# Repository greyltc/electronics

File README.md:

# solar-sim-electronics
KiCAD electrical circuit design and PCB layout files for solar cell measurement equipment

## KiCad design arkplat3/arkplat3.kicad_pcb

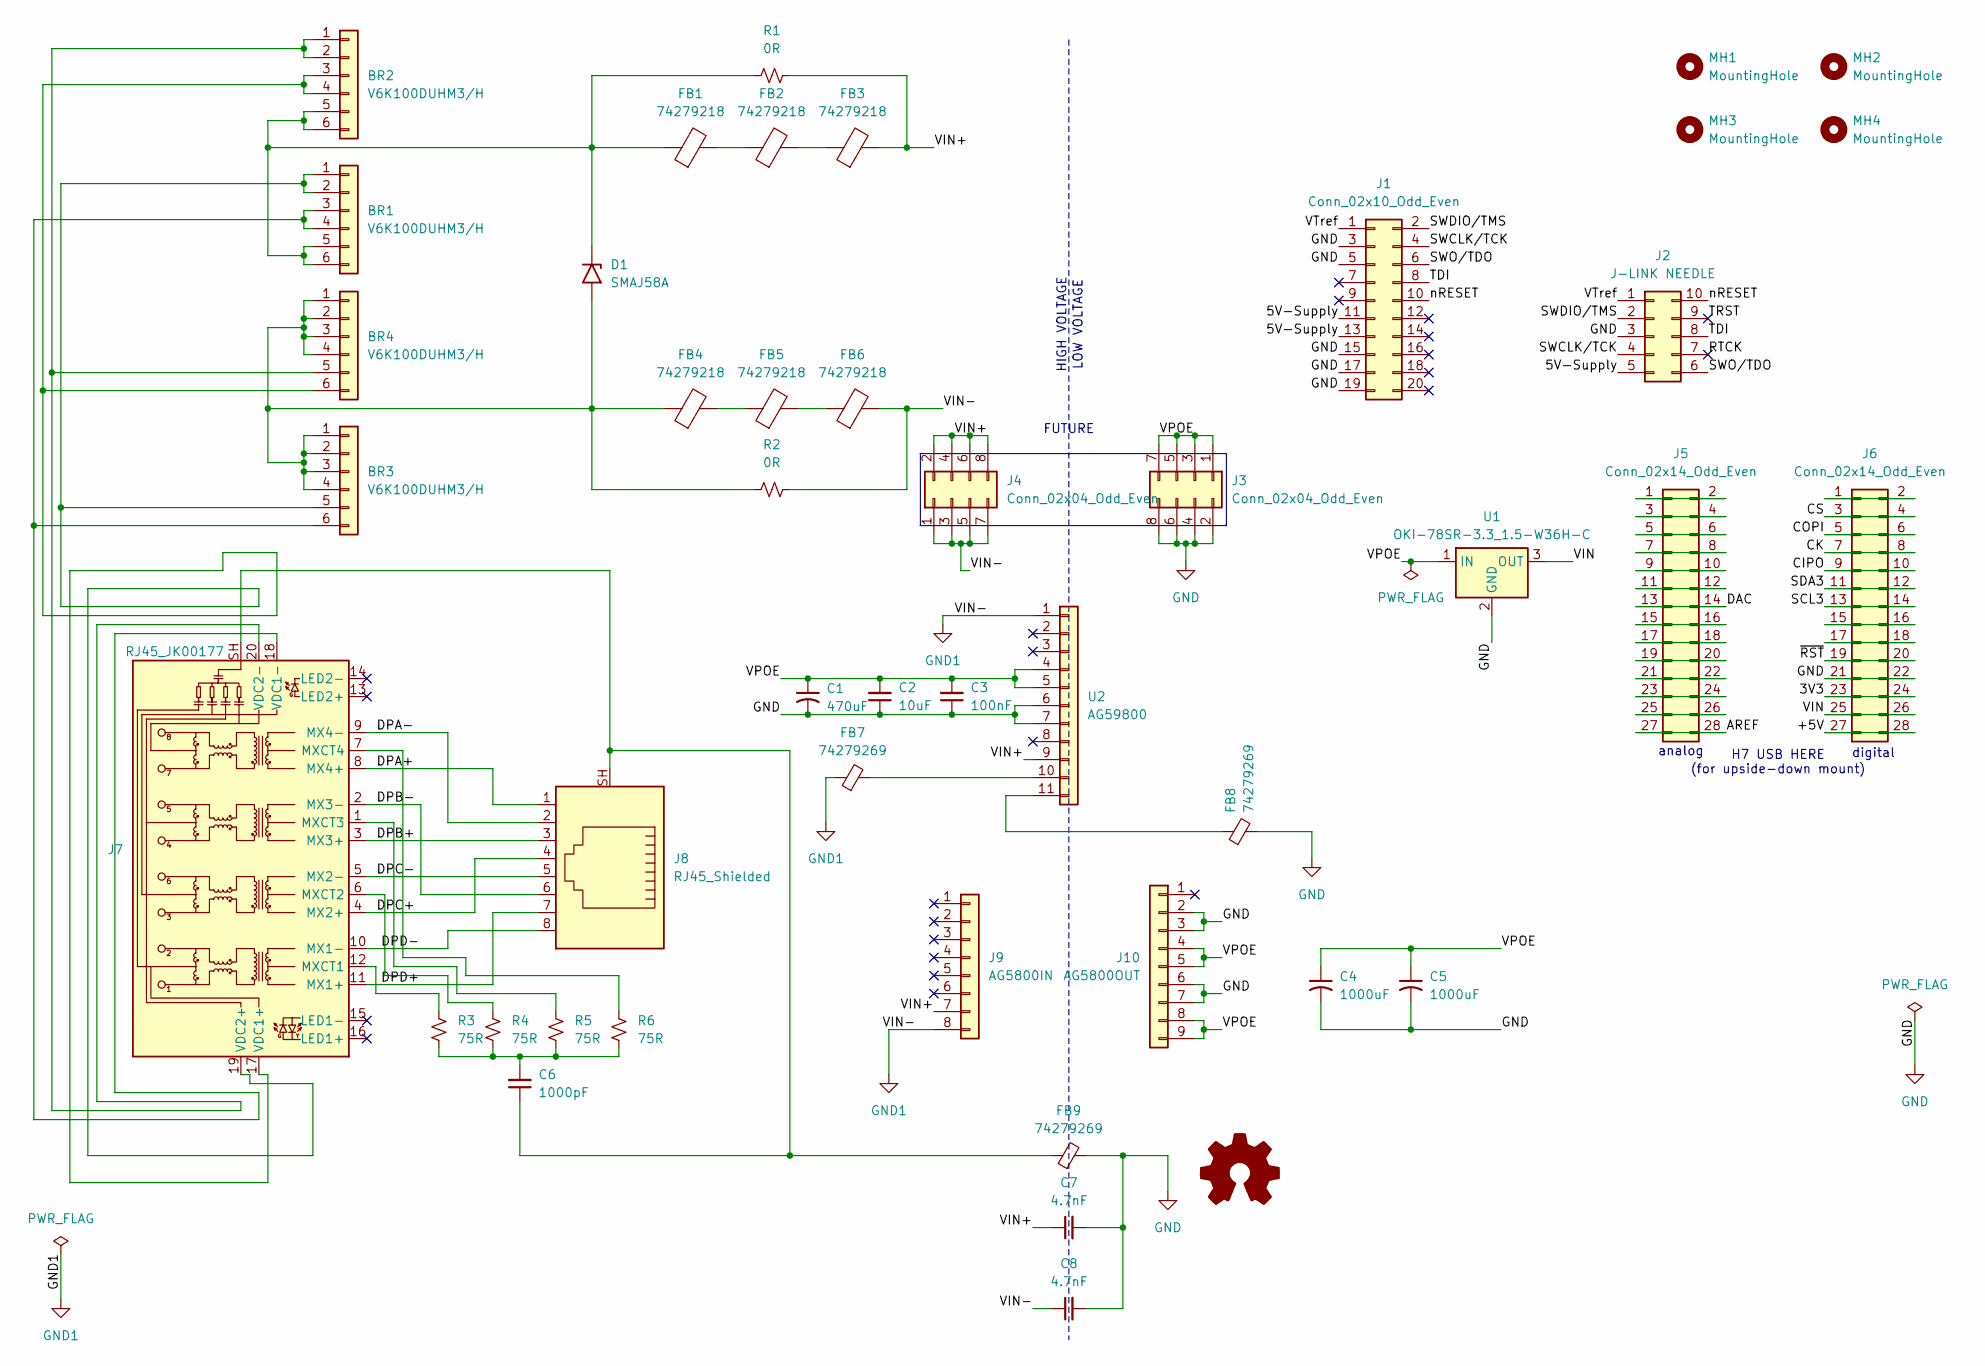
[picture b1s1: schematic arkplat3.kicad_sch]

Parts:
BR1, BR2, BR3, BR4: V6K100DUHM3/H; PowerPAK_SO-8_Dual
C1: 470uF; CP_Radial_D10.0mm_P5.00mm
C2: 10uF; C_1206_3216Metric_Pad1.33x1.80mm_HandSolder
C3: 100nF; C_1206_3216Metric_Pad1.33x1.80mm_HandSolder
C4, C5: 1000uF; CP_Radial_D10.0mm_P5.00mm
C6: 1000pF; C_1206_3216Metric_Pad1.33x1.80mm_HandSolder
C7, C8: 4.7nF; C_1206_3216Metric_Pad1.33x1.80mm_HandSolder
D1: SMAJ58A; D_SMA
FB1, FB2, FB3, FB4, FB5, FB6: 74279218; L_1206_3216Metric_Pad1.22x1.90mm_HandSolder
FB7, FB8, FB9: 74279269; L_0603_1608Metric_Pad1.05x0.95mm_HandSolder
J1: Conn_02x10_Odd_Even; PinHeader_2x10_P1.27mm_Vertical_SMD
J2: J-LINK NEEDLE; Tag-Connect_TC2050-IDC-FP_2x05_P1.27mm_Vertical
J3, J4: Conn_02x04_Odd_Even; PinSocket_2x04_P2.54mm_Vertical
J5, J6: Conn_02x14_Odd_Even; PinSocket_2x14_P2.54mm_Vertical
J7: RJ45_JK00177; RJ45_Pulse_JK00177NL_Horizontal
J8: RJ45_Shielded; RJ45_Molex_0855135013_Vertical
J9: AG5800IN; PinSocket_1x08_P2.54mm_Vertical
J10: AG5800OUT; PinSocket_1x09_P2.54mm_Vertical
MH1, MH2, MH3, MH4: MountingHole; MountingHole_2.7mm_M2.5_ISO14580
R1, R2: 0R; R_1206_3216Metric_Pad1.30x1.75mm_HandSolder
R3, R4, R5, R6: 75R; R_1206_3216Metric_Pad1.30x1.75mm_HandSolder
SYM1: Logo_Open_Hardware_Small; site_small
U1: OKI-78SR-3.3_1.5-W36H-C; Converter_DCDC_Murata_OKI-78SR_Horizontal
U2: AG59800; AG59800-LPB

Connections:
/3V3: J6.23, J6.24
/5V-Supply: J1.11, J1.13, J2.5
/+5V: J6.27, J6.28
/AREF: J5.27, J5.28
/CIPO: J6.9, J6.10
/CK: J6.7, J6.8
/COPI: J6.5, J6.6
/CS: J6.3, J6.4
/DAC: J5.13, J5.14
/DPA+: J7.8 (MX4+), J8.1
/DPA-: J7.9 (MX4-), J8.2
/DPB+: J7.3 (MX3+), J8.3
/DPB-: J7.2 (MX3-), J8.6
/DPC+: J7.4 (MX2+), J8.4
/DPC-: J7.5 (MX2-), J8.5
/DPD+: J7.11 (MX1+), J8.7
/DPD-: J7.10 (MX1-), J8.8
/RTCK: J2.7
/SCL3: J6.13, J6.14
/SDA3: J6.11, J6.12
/SWCLK/TCK: J1.4, J2.4
/SWDIO/TMS: J1.2, J2.2
/SWO/TDO: J1.6, J2.6
/TDI: J1.8, J2.8
/TRST: J2.9
/VIN: J6.25, J6.26, U1.3 (OUT)
/VIN+: C7.1, FB3.2, J4.2, J4.4, J4.6, J4.8, J9.7, R1.2, U2.9
/VPOE: C1.1, C2.2, C3.2, C4.1, C5.1, J3.1, J3.3, J3.5, J3.7, J10.4, J10.5, J10.8, J10.9, U1.1 (IN), U2.4, U2.5
/VTref: J1.1, J2.1
/nRESET: J1.10, J2.10
/~RST: J6.19, J6.20
GND: C1.2, C2.1, C3.1, C4.2, C5.2, C7.2, C8.2, FB8.2, FB9.2, J1.3, J1.5, J1.15, J1.17, J1.19, J2.3, J3.2, J3.4, J3.6, J3.8, J6.21, J6.22, J10.2, J10.3, J10.6, J10.7, U1.2 (GND), U2.6, U2.7
GND1: C8.1, FB6.2, FB7.1, J4.1, J4.3, J4.5, J4.7, J9.8, R2.2, U2.1
unnamed: BR1.1, BR1.2, BR3.5, J7.19 (VDC2+)
unnamed: BR1.3, BR1.4, BR3.6, J7.18 (VDC1-)
unnamed: BR1.5, BR1.6, BR2.5, BR2.6, D1.1 (A1), FB1.1, R1.1
unnamed: BR2.1, BR2.2, BR4.5, J7.20 (VDC2-)
unnamed: BR2.3, BR2.4, BR4.6, J7.17 (VDC1+)
unnamed: BR3.1, BR3.2, BR3.3, BR3.4, BR4.1, BR4.2, BR4.3, BR4.4, D1.2 (A2), FB4.1, R2.1
unnamed: C6.1, FB9.1, J7.SH, J8.SH
unnamed: C6.2, R3.2, R4.2, R5.2, R6.2
unnamed: FB1.2, FB2.1
unnamed: FB2.2, FB3.1
unnamed: FB4.2, FB5.1
unnamed: FB5.2, FB6.1
unnamed: J5.1, J5.2
unnamed: J5.3, J5.4
unnamed: J5.5, J5.6
unnamed: J5.7, J5.8
unnamed: J5.9, J5.10
unnamed: J5.11, J5.12
unnamed: J5.15, J5.16
unnamed: J5.17, J5.18
unnamed: J5.19, J5.20
unnamed: J5.21, J5.22
unnamed: J5.23, J5.24
unnamed: J5.25, J5.26
unnamed: J6.1, J6.2
unnamed: J6.15, J6.16
unnamed: J6.17, J6.18
unnamed: J7.12 (MXCT1), R3.1
unnamed: J7.6 (MXCT2), R4.1
unnamed: J7.1 (MXCT3), R5.1
unnamed: J7.7 (MXCT4), R6.1
unnamed: FB7.2, U2.10
unnamed: FB8.1, U2.11

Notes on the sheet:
FUTURE
LOW VOLTAGE
H7 USB HERE (for upside-down mount)
digital
HIGH VOLTAGE
analog

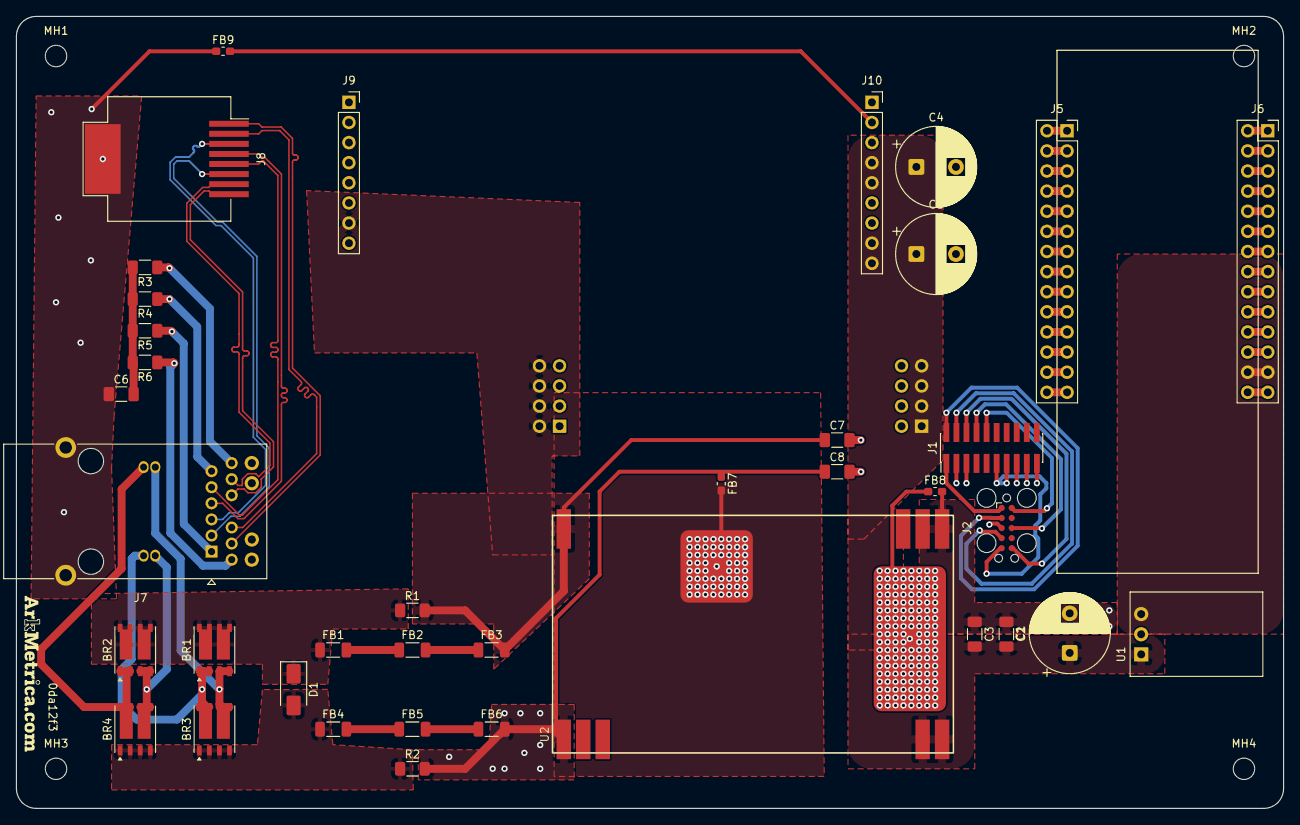
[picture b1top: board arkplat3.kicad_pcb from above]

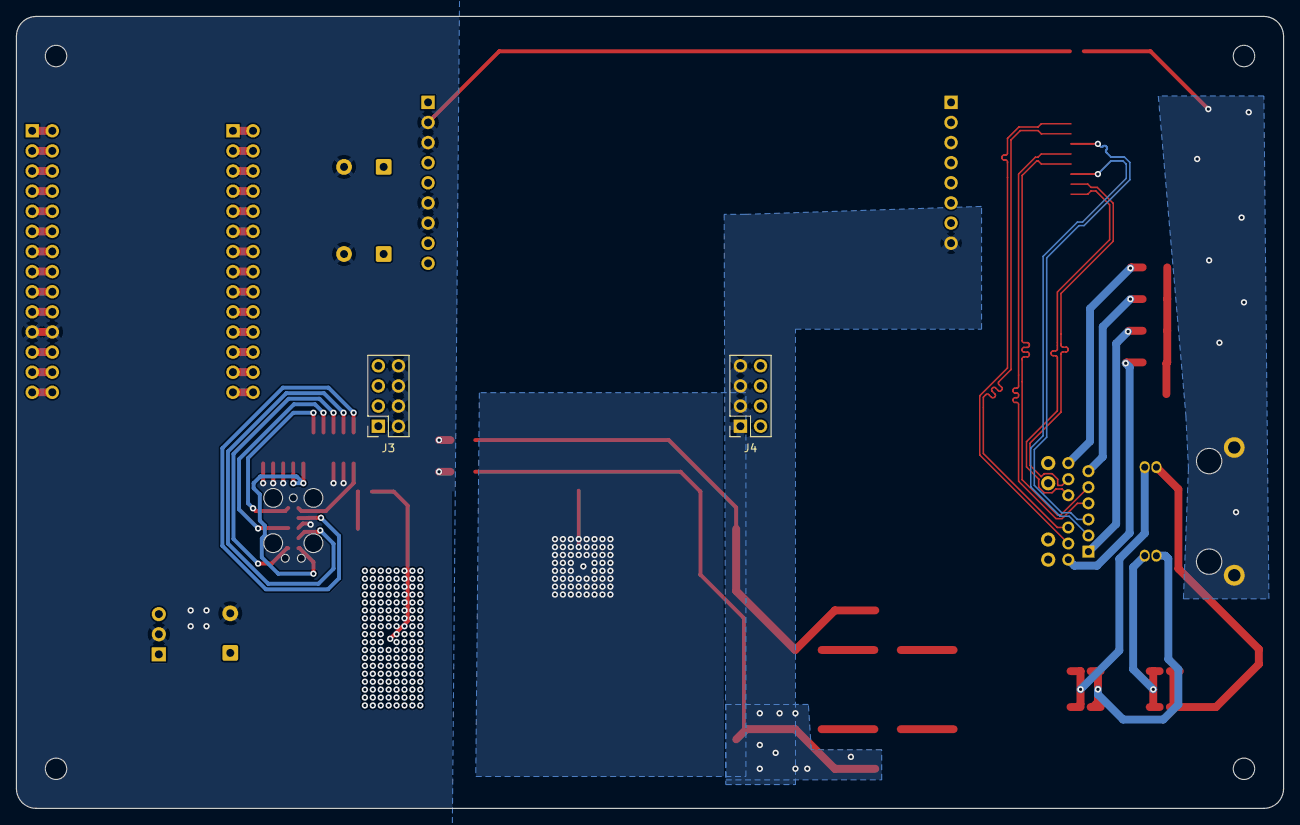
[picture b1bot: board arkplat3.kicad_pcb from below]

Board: 2 copper layers, 160.0 x 100.0 mm, 45 parts (2 on the bottom side), 64 nets.

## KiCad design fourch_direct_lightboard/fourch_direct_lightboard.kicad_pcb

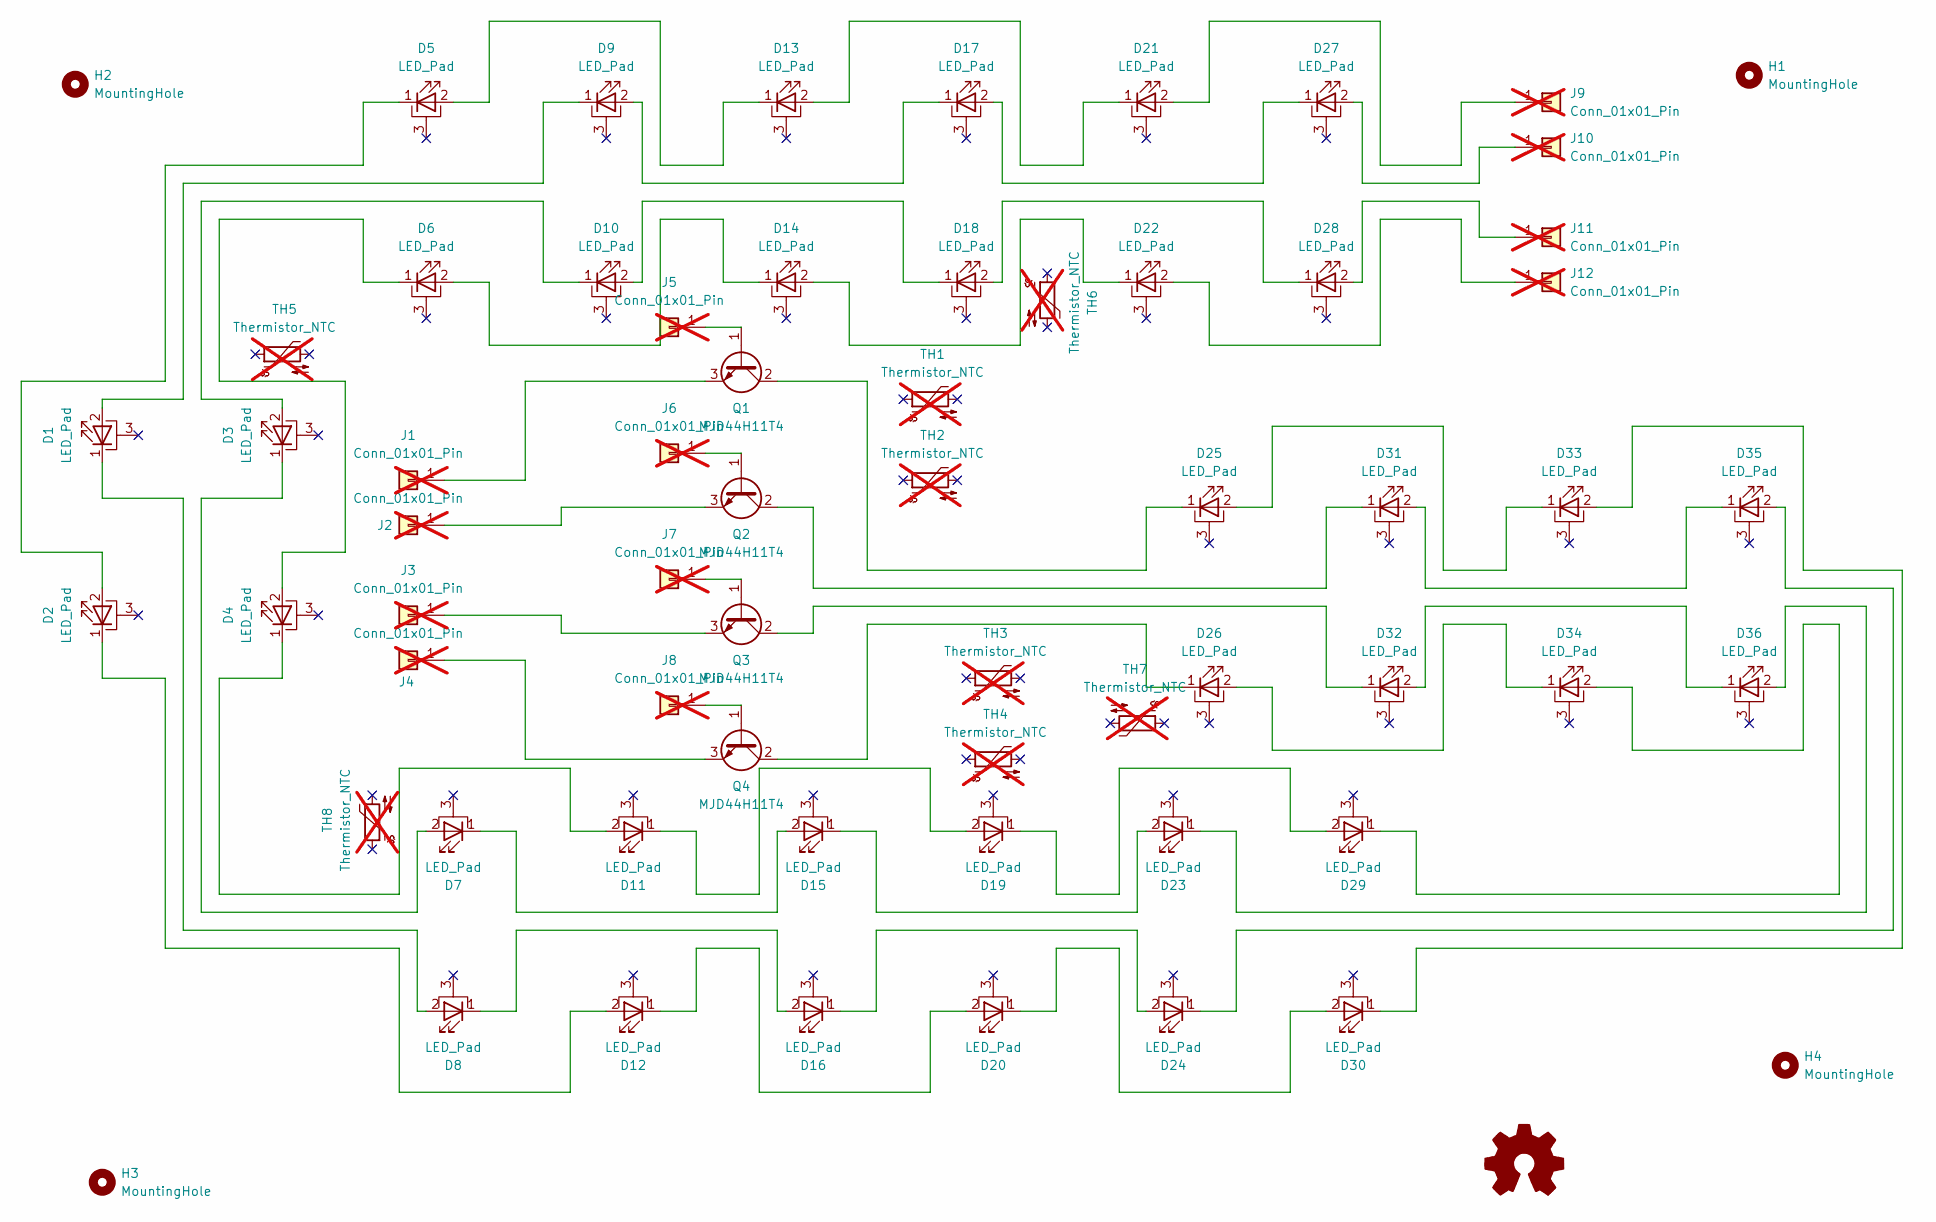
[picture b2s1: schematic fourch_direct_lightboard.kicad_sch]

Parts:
D1, D2, D3, D4, D5, D6, D7, D8, D9, D10, D11, D12, D13, D14, D15, D16, D17, D18, D19, D20, D21, D22, D23, D24, D25, D26, D27, D28, D29, D30, D31, D32, D33, D34, D35, D36: LED_Pad; LED_3x3_DIRECT_CU
H1, H2, H3, H4: MountingHole; MountingHole_3.50mm
J1, J2, J3, J4, J5, J6, J7, J8, J9, J10, J11, J12: Conn_01x01_Pin; TestPoint_Pad_D1.5mm; not fitted
Q1, Q2, Q3, Q4: MJD44H11T4; TO-252-2
SYM4: Logo_Open_Hardware_Small; site_small
TH1, TH2, TH3, TH4, TH5, TH6, TH7, TH8: Thermistor_NTC; R_0805_2012Metric_Pad1.20x1.40mm_HandSolder; not fitted

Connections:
unnamed: D1.2 (A), D9.1 (K)
unnamed: D1.1 (K), D8.2 (A)
unnamed: D2.2 (A), D5.1 (K)
unnamed: D3.1 (K), D7.2 (A)
unnamed: D4.2 (A), D6.1 (K)
unnamed: D10.2 (A), D18.1 (K)
unnamed: D3.2 (A), D10.1 (K)
unnamed: D4.1 (K), D11.2 (A)
unnamed: D11.1 (K), D19.2 (A)
unnamed: D2.1 (K), D12.2 (A)
unnamed: D12.1 (K), D20.2 (A)
unnamed: D13.2 (A), D21.1 (K)
unnamed: D5.2 (A), D13.1 (K)
unnamed: D14.2 (A), D22.1 (K)
unnamed: D6.2 (A), D14.1 (K)
unnamed: D7.1 (K), D15.2 (A)
unnamed: D15.1 (K), D23.2 (A)
unnamed: D8.1 (K), D16.2 (A)
unnamed: D16.1 (K), D24.2 (A)
unnamed: D17.2 (A), D27.1 (K)
unnamed: D9.2 (A), D17.1 (K)
unnamed: D18.2 (A), D28.1 (K)
unnamed: D19.1 (K), D29.2 (A)
unnamed: D20.1 (K), D30.2 (A)
unnamed: D21.2 (A), J9.1
unnamed: D22.2 (A), J12.1
unnamed: D23.1 (K), D36.2 (A)
unnamed: D24.1 (K), D35.2 (A)
unnamed: D25.2 (A), D33.1 (K)
unnamed: D25.1 (K), Q1.2 (C)
unnamed: D26.2 (A), D34.1 (K)
unnamed: D26.1 (K), Q4.2 (C)
unnamed: D27.2 (A), J10.1
unnamed: D28.2 (A), J11.1
unnamed: D29.1 (K), D34.2 (A)
unnamed: D30.1 (K), D33.2 (A)
unnamed: D31.2 (A), D35.1 (K)
unnamed: D31.1 (K), Q2.2 (C)
unnamed: D32.2 (A), D36.1 (K)
unnamed: D32.1 (K), Q3.2 (C)
unnamed: J1.1, Q1.3 (E)
unnamed: J2.1, Q2.3 (E)
unnamed: J3.1, Q3.3 (E)
unnamed: J4.1, Q4.3 (E)
unnamed: J5.1, Q1.1 (B)
unnamed: J6.1, Q2.1 (B)
unnamed: J7.1, Q3.1 (B)
unnamed: J8.1, Q4.1 (B)

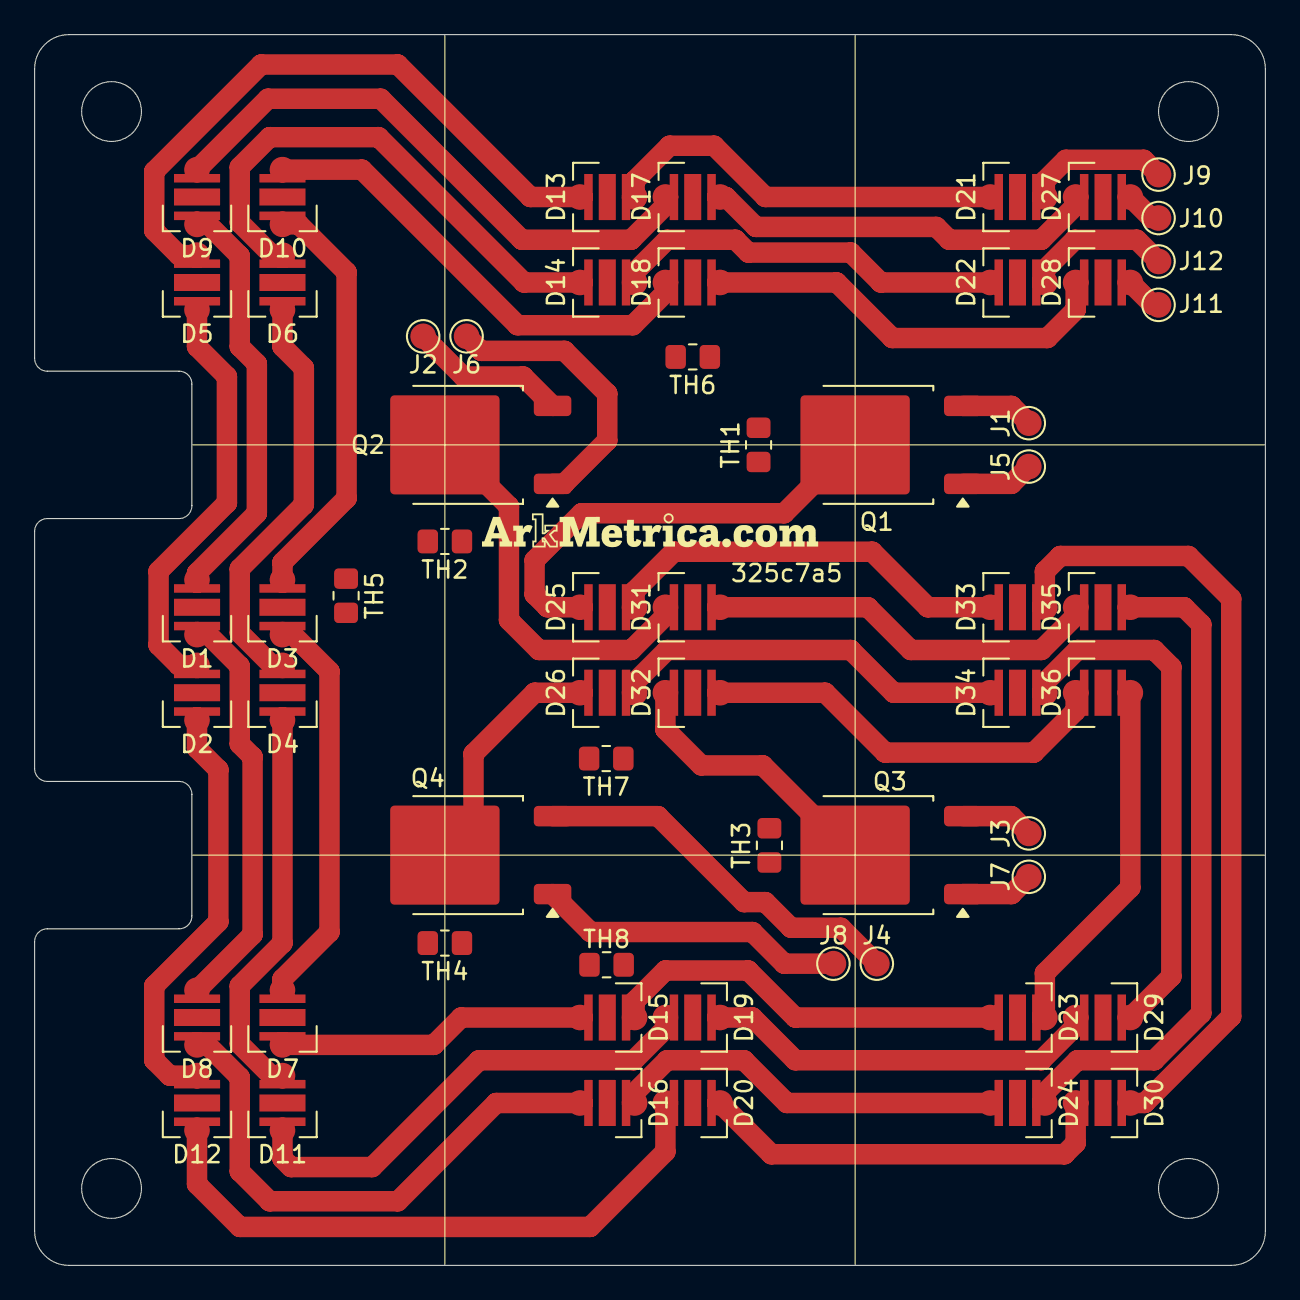
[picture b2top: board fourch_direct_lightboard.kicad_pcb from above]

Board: 2 copper layers, 72.0 x 72.0 mm, 65 parts (0 on the bottom side), 48 nets.

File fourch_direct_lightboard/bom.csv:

Comment,Designator,Footprint,LCSC Part Number
SST-10-UV-B130-F365-00,"D21,D13,D5,D2,D12,D20,D30,D33,D25",1212 LED THERMAL PAD,C6496960
SST-10-IRD-B130H-S810,"D27,D17,D9,D1,D8,D16,D24,D35,D31",1212 LED THERMAL PAD,C5291399
SST-10-IRD-B130H-S940,"D28,D18,D10,D3,D7,D15,D23,D36,D32",1212 LED THERMAL PAD,C7322031
GW CSSRM3.CM-M9N4-XX53-1-700-R18,"D22,D14,D6,D4,D11,D19,D29,D34,D26",1212 LED THERMAL PAD,C17379658
NSS1C301ET4G,"Q1,Q2,Q3,Q4",TO-252(DPAK),C463629

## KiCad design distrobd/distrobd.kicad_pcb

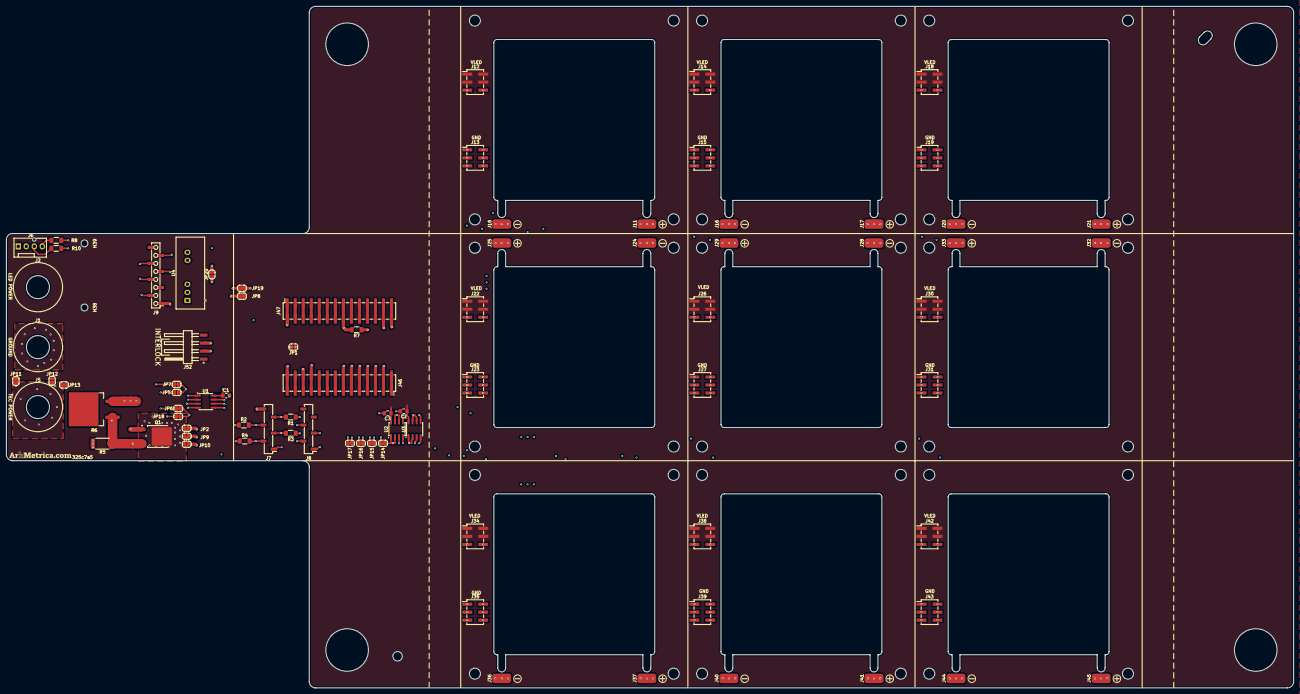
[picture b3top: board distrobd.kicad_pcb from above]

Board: 4 copper layers, 408.0 x 216.0 mm, 125 parts (0 on the bottom side), 58 nets.

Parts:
C1, C2, C3: 0.1uF; C_0805_2012Metric_Pad1.18x1.45mm_HandSolder
H1, H2, H3, H4, H5, H6, H7, H8, H9, H10, H11, H12, H13, H14, H15, H16, H17, H18, H19, H20, H21, H22, H23, H24, H25, H26, H27, H28, H29, H30, H31, H32, H33, H34, H35, H36: MountingHole; MountingHole_3.50mm
H37: MountingHole; MountingHole_3.0mm
H38, H39: MountingHole; MountingHole_2.2mm_M2
H40, H41, H42, H43: MountingHole; 13.5mm_NPTH
J1, J2, J5: Conn_01x01; LF994006
J6: Conn_01x04; FanPinHeader_1x04_P2.54mm_Vertical
J7, J8: Conn_01x06; PinSocket_1x06_P2.54mm_Vertical_SMD_Pin1Left
J9: Conn_01x08; PinSocket_1x08_P2.54mm_Vertical_SMD_Pin1Left
J10, J11, J16, J17, J20, J21, J24, J25, J28, J29, J32, J33, J36, J37, J40, J41, J44, J45: Conn_01x01; SolderWirePad_1x01_SMD_3x6mm
J12, J13, J14, J15, J18, J19, J22, J23, J26, J27, J30, J31, J34, J35, J38, J39, J42, J43: Conn_02x03_Odd_Even; PinHeader_2x03_P2.54mm_Vertical_SMD
J46, J47: Conn_02x14_Top_Bottom; PinSocket_2x14_P2.54mm_Vertical_SMD
J52: Conn_01x04; Harwin_M20-89004xx_1x04_P2.54mm_Horizontal
JP1, JP6, JP7: SolderJumper_2_Bridged; SolderJumper-2_P1.3mm_Bridged_RoundedPad1.0x1.5mm
JP2, JP5, JP9, JP10, JP11, JP12, JP13, JP14, JP15, JP16, JP17, JP18, JP19, JP20: SolderJumper_2_Open; SolderJumper-2_P1.3mm_Open_RoundedPad1.0x1.5mm
JP8: SolderJumper_2_Bridged; SolderJumper-2_P1.3mm_Bridged2Bar_RoundedPad1.0x1.5mm
Q1: Q_NPN_CBE; TO-252-2
R1, R2, R3, R4: 4k7; R_1206_3216Metric_Pad1.30x1.75mm_HandSolder
R5: 2R; R_2512_6332Metric_Pad1.40x3.35mm_HandSolder
R6: 2R; TO-263-2_TabPin1
R7: 100K; R_1206_3216Metric_Pad1.30x1.75mm_HandSolder
R8, R10: 0R; R_1206_3216Metric_Pad1.30x1.75mm_HandSolder
SYM1: Logo_Open_Hardware_Small; site_small
U1, U2, U3: OPA2994xD; SOIC-8_3.9x4.9mm_P1.27mm
U4: NCS1S2412SC; Converter_DCDC_Murata_NCS1SxxxxSC_THT

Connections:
/3V3: J46.23, J46.24, JP1.1 (A)
/12V_FAN_POWER: J6.2, U4.6 (+VOUT)
/+5V: J9.1, J46.27, J46.28, J52.3
/+5V_LOCK: J7.6, J8.1, J52.2
/AREF: J47.1, J47.2, JP1.2 (B)
/CIPO: J9.5, J46.9, J46.10
/CK: J9.4, J46.7, J46.8
/COPI: J9.6, J46.5, J46.6
/CS: J9.7, J46.3, J46.4
/FAN_GND: J6.1, JP20.2 (B), U4.7 (-VOUT)
/FAN_PWM: J47.27, J47.28, R8.2
/FAN_TACH: J47.25, J47.26, R10.2
/GND: C1.2, C2.2, C3.2, J7.1, J8.2, J9.2, J13.1, J13.2, J13.3, J13.4, J15.1, J15.2, J15.3, J15.4, J19.1, J19.2, J19.3, J19.4, J23.1, J23.2, J23.3, J23.4, J27.1, J27.2, J27.3, J27.4, J31.1, J31.2, J31.3, J31.4, J35.1, J35.2, J35.3, J35.4, J39.1, J39.2, J39.3, J39.4, J43.1, J43.2, J43.3, J43.4, J46.21, J46.22, JP2.2 (B), JP9.2 (B), JP10.2 (B), JP18.2 (B), JP20.1 (A), R1.1, R2.1, R3.1, R4.1, R5.2, R6.2, R7.1, U1.4 (V-), U2.4 (V-), U3.4 (V-), U4.1 (-VIN)
/SCL3: J8.3, J46.13, J46.14
/SDA3: J8.4, J46.11, J46.12
/TEC_DAC: J47.15, J47.16, JP5.2 (B), JP6.1 (A), R7.2
/VA: J12.5, J14.5, J18.5, J22.5, J26.5, J30.5, J34.5, J38.5, J42.5, JP14.2 (B), U2.1, U2.2 (-)
/VAR: J7.2, JP14.1 (A), R4.2, U2.3 (+)
/VB: J12.6, J14.6, J18.6, J22.6, J26.6, J30.6, J34.6, J38.6, J42.6, JP15.2 (B), U2.6 (-), U2.7
/VBR: J7.3, JP15.1 (A), R3.2, U2.5 (+)
/VC: J13.5, J15.5, J19.5, J23.5, J27.5, J31.5, J35.5, J39.5, J43.5, JP16.2 (B), U3.1, U3.2 (-)
/VCR: J7.4, JP16.1 (A), R2.2, U3.3 (+)
/VD: J13.6, J15.6, J19.6, J23.6, J27.6, J31.6, J35.6, J39.6, J43.6, JP17.2 (B), U3.6 (-), U3.7
/VDR: J7.5, JP17.1 (A), R1.2, U3.5 (+)
/VIN: J46.25, J46.26
/VLED: C2.1, C3.1, J12.1, J12.2, J12.3, J12.4, J14.1, J14.2, J14.3, J14.4, J18.1, J18.2, J18.3, J18.4, J22.1, J22.2, J22.3, J22.4, J26.1, J26.2, J26.3, J26.4, J30.1, J30.2, J30.3, J30.4, J34.1, J34.2, J34.3, J34.4, J38.1, J38.2, J38.3, J38.4, J42.1, J42.2, J42.3, J42.4, JP8.2 (B), JP11.1 (A), JP12.1 (A), JP13.1 (A), U2.8 (V+), U3.8 (V+)
/VTEC: C1.1, J45.1, JP11.2 (B), JP12.2 (B), JP13.2 (B), JP19.2 (B), U1.8 (V+)
/VTEC_LO: J10.1, JP2.1 (A), JP9.1 (A), JP10.1 (A), Q1.2 (C)
/~RST: J46.19, J46.20
unnamed: J6.3, R10.1
unnamed: J6.4, R8.1
unnamed: J11.1, J16.1
unnamed: J17.1, J20.1
unnamed: J21.1, J32.1
unnamed: J24.1, J29.1
unnamed: J25.1, J36.1
unnamed: J28.1, J33.1
unnamed: J37.1, J40.1
unnamed: J41.1, J44.1
unnamed: J46.1, J46.2
unnamed: J46.15, J46.16
unnamed: J46.17, J46.18
unnamed: J47.3, J47.4
unnamed: J47.5, J47.6
unnamed: J47.7, J47.8
unnamed: J47.9, J47.10
unnamed: J47.11, J47.12
unnamed: J47.13, J47.14
unnamed: J47.17, J47.18
unnamed: J47.19, J47.20
unnamed: J47.21, J47.22
unnamed: J47.23, J47.24
unnamed: JP5.1 (A), JP7.2 (B), U1.3 (+)
unnamed: JP7.1 (A), U1.6 (-), U1.7
unnamed: JP6.2 (B), JP18.1 (A), U1.5 (+)
unnamed: JP8.1 (A), JP19.1 (A), U4.2 (+VIN)
unnamed: Q1.1 (B), U1.1
unnamed: Q1.3 (E), R5.1, R6.1, U1.2 (-)

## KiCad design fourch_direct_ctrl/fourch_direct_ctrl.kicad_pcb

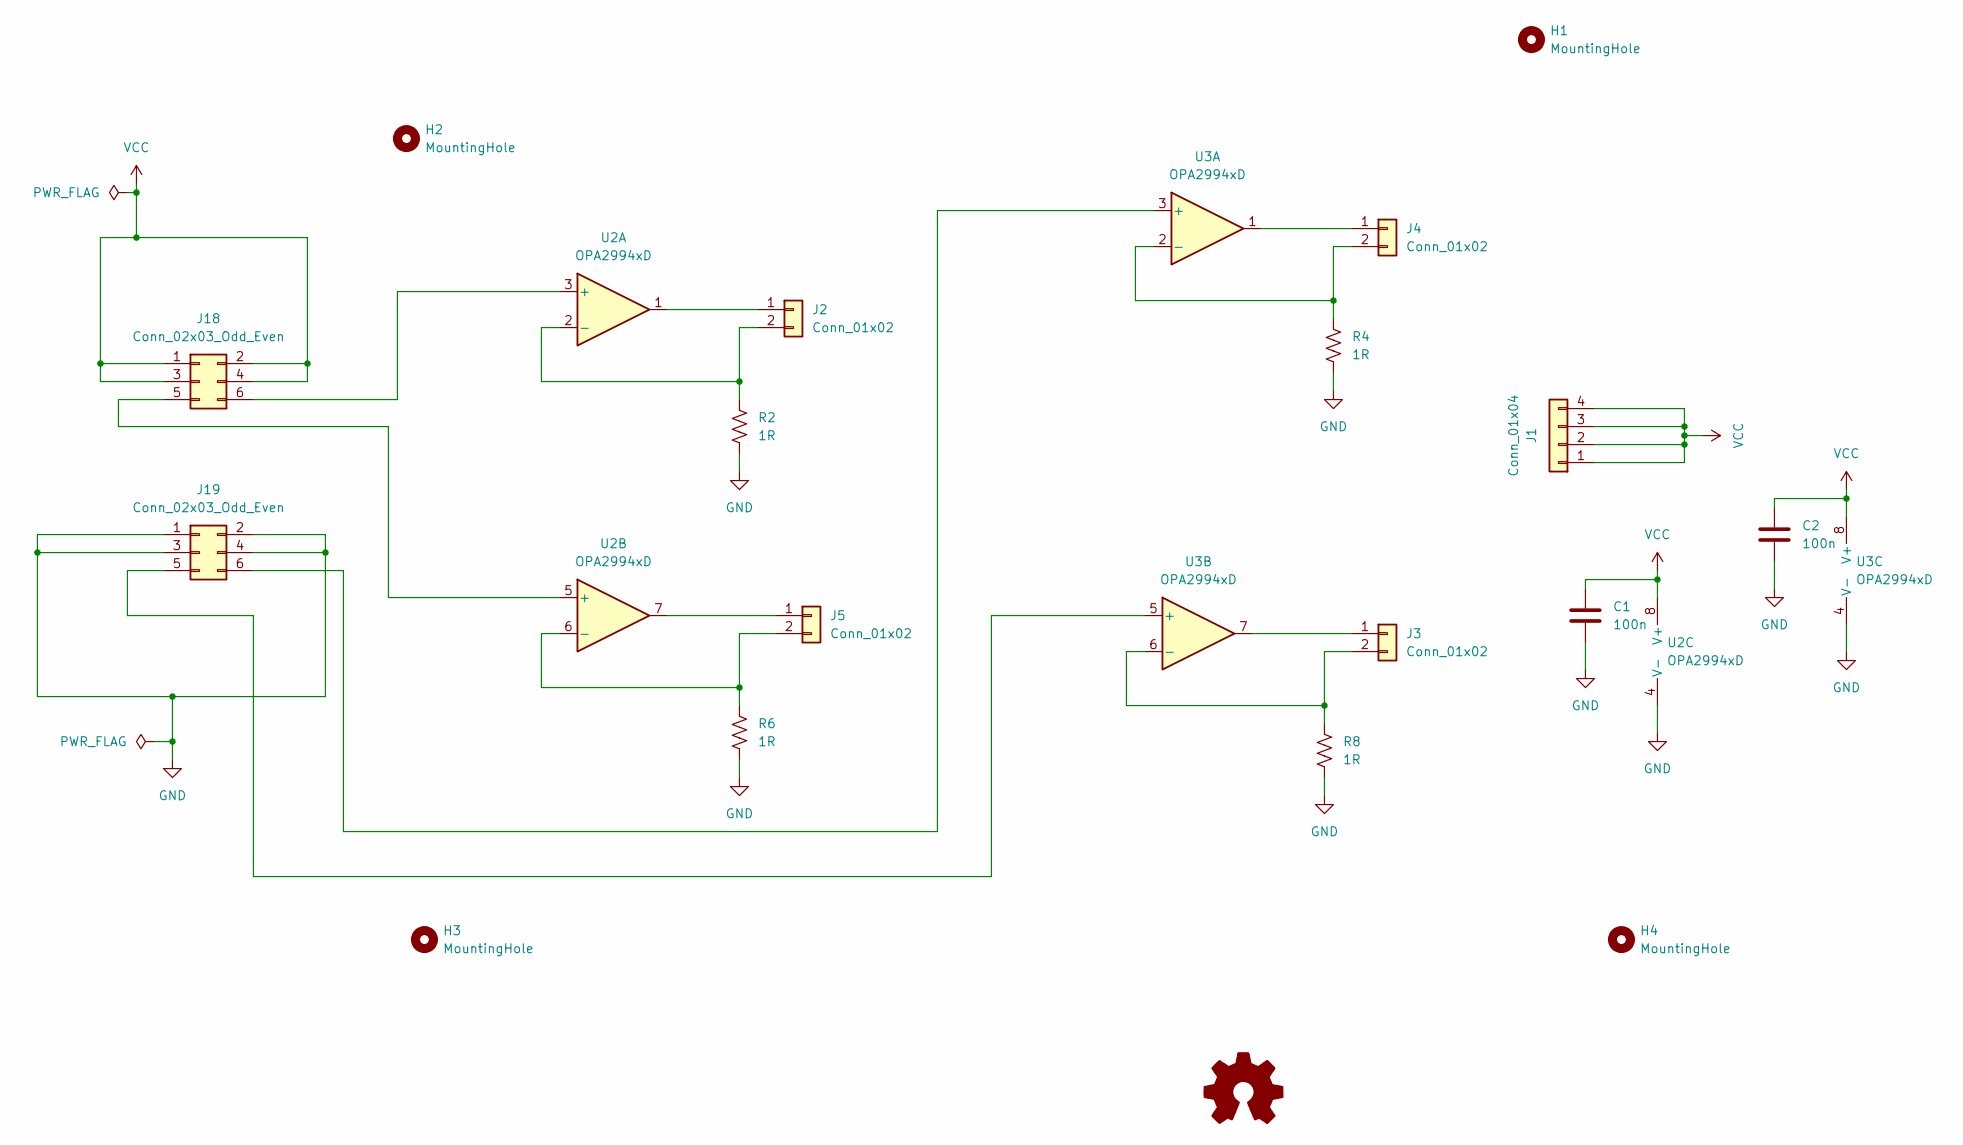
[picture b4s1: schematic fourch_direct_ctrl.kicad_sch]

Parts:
C1, C2: 100n; C_0805_2012Metric_Pad1.18x1.45mm_HandSolder
H1, H2, H3, H4: MountingHole; MountingHole_3.45mm
J1: Conn_01x04; PinHeader_1x04_P2.54mm_Vertical
J2, J3, J4, J5: Conn_01x02; PinHeader_1x02_P2.54mm_Vertical
J18, J19: Conn_02x03_Odd_Even; Wuerth_WR-PHD_610006243021_SMD_2x03_P2.54mm_Vertical
R2, R4, R6, R8: 1R; R_2512_6332Metric_Pad1.40x3.35mm_HandSolder
SYM1: Logo_Open_Hardware_Small; site_small
U2, U3: OPA2994xD; SOIC-8_3.9x4.9mm_P1.27mm

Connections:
GND: C1.2, C2.2, J19.1, J19.2, J19.3, J19.4, R2.2, R4.2, R6.2, R8.2, U2.4 (V-), U3.4 (V-)
unnamed: J2.1, U2.1
unnamed: J2.2, R2.1, U2.2 (-)
unnamed: J3.1, U3.7
unnamed: J3.2, R8.1, U3.6 (-)
unnamed: J4.1, U3.1
unnamed: J4.2, R4.1, U3.2 (-)
unnamed: J5.1, U2.7
unnamed: J5.2, R6.1, U2.6 (-)
unnamed: J18.5, U2.5 (+)
unnamed: J18.6, U2.3 (+)
unnamed: J19.5, U3.5 (+)
unnamed: J19.6, U3.3 (+)
VCC: C1.1, C2.1, J1.1, J1.2, J1.3, J1.4, J18.1, J18.2, J18.3, J18.4, U2.8 (V+), U3.8 (V+)

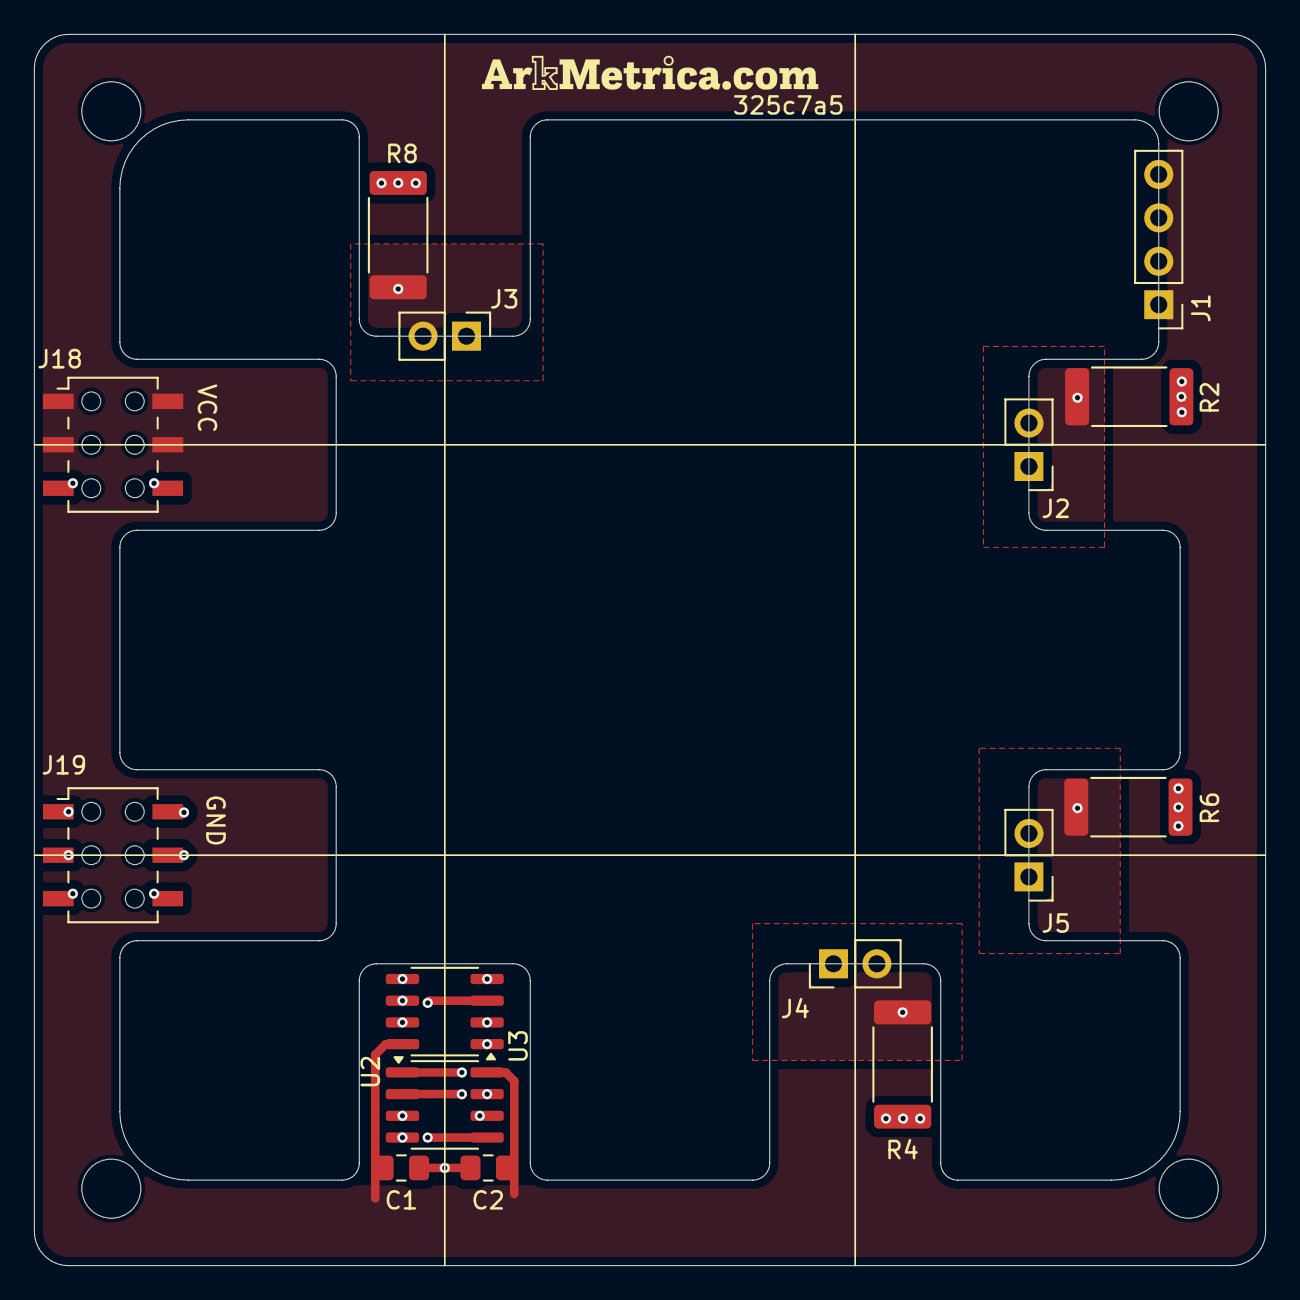
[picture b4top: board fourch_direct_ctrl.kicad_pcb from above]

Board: 4 copper layers, 72.0 x 72.0 mm, 20 parts (0 on the bottom side), 14 nets.

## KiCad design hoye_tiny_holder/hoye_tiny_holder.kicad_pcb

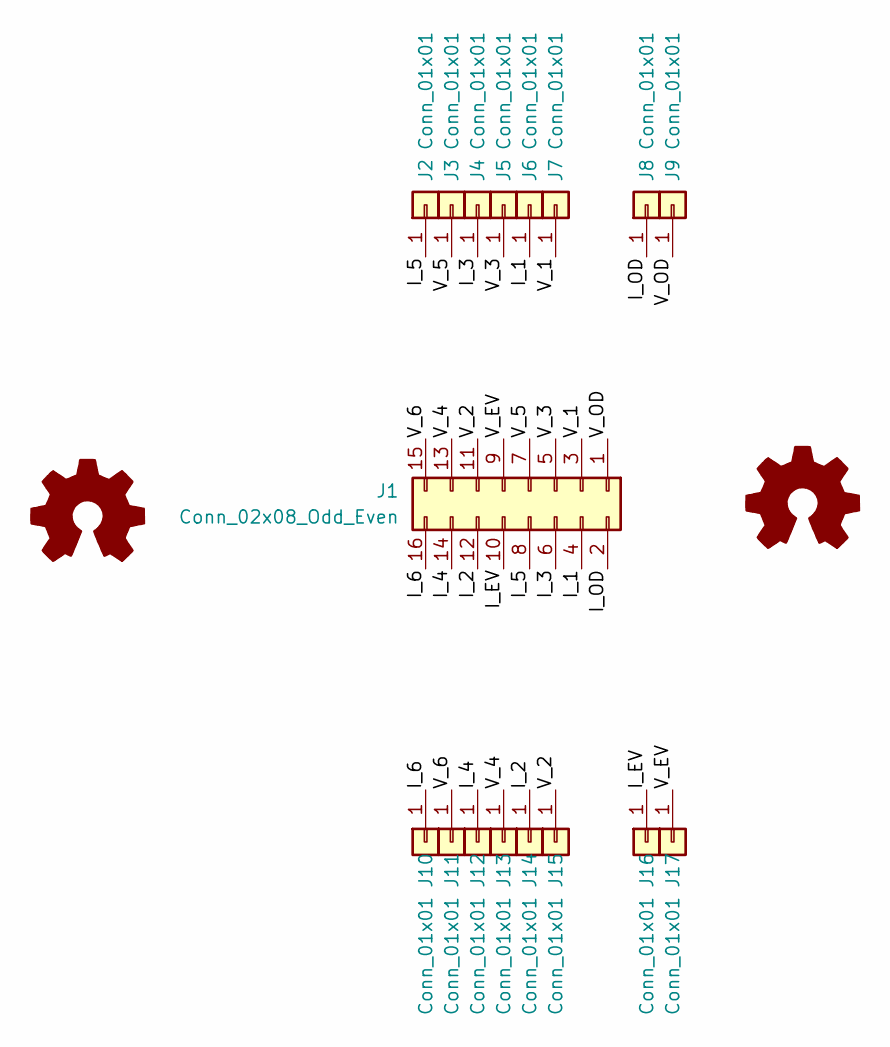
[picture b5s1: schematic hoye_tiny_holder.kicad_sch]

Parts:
J1: Conn_02x08_Odd_Even; IDC-Header_2x08_P2.54mm_Vertical
J2, J3, J4, J5, J6, J7, J8, J9, J10, J11, J12, J13, J14, J15, J16, J17: Conn_01x01; P13-4023+S13-503_OFF
SYM1, SYM2: Logo_Open_Hardware_Small; site_small

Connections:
/I_1: J1.4, J6.1
/I_2: J1.12, J14.1
/I_3: J1.6, J4.1
/I_4: J1.14, J12.1
/I_5: J1.8, J2.1
/I_6: J1.16, J10.1
/I_EV: J1.10, J16.1
/I_OD: J1.2, J8.1
/V_1: J1.3, J7.1
/V_2: J1.11, J15.1
/V_3: J1.5, J5.1
/V_4: J1.13, J13.1
/V_5: J1.7, J3.1
/V_6: J1.15, J11.1
/V_EV: J1.9, J17.1
/V_OD: J1.1, J9.1

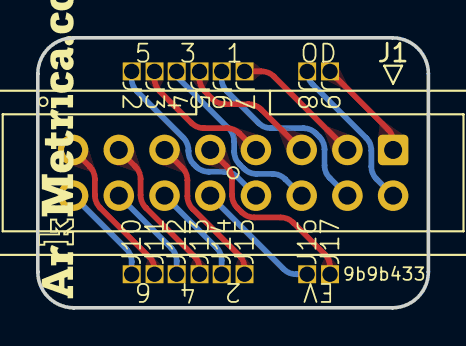
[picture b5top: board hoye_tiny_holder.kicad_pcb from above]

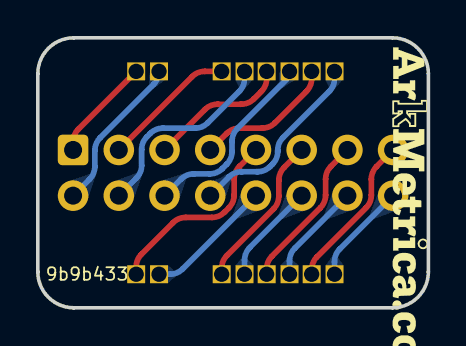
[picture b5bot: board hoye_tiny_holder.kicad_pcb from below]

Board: 2 copper layers, 21.7 x 15.0 mm, 19 parts (17 on the bottom side), 16 nets.
